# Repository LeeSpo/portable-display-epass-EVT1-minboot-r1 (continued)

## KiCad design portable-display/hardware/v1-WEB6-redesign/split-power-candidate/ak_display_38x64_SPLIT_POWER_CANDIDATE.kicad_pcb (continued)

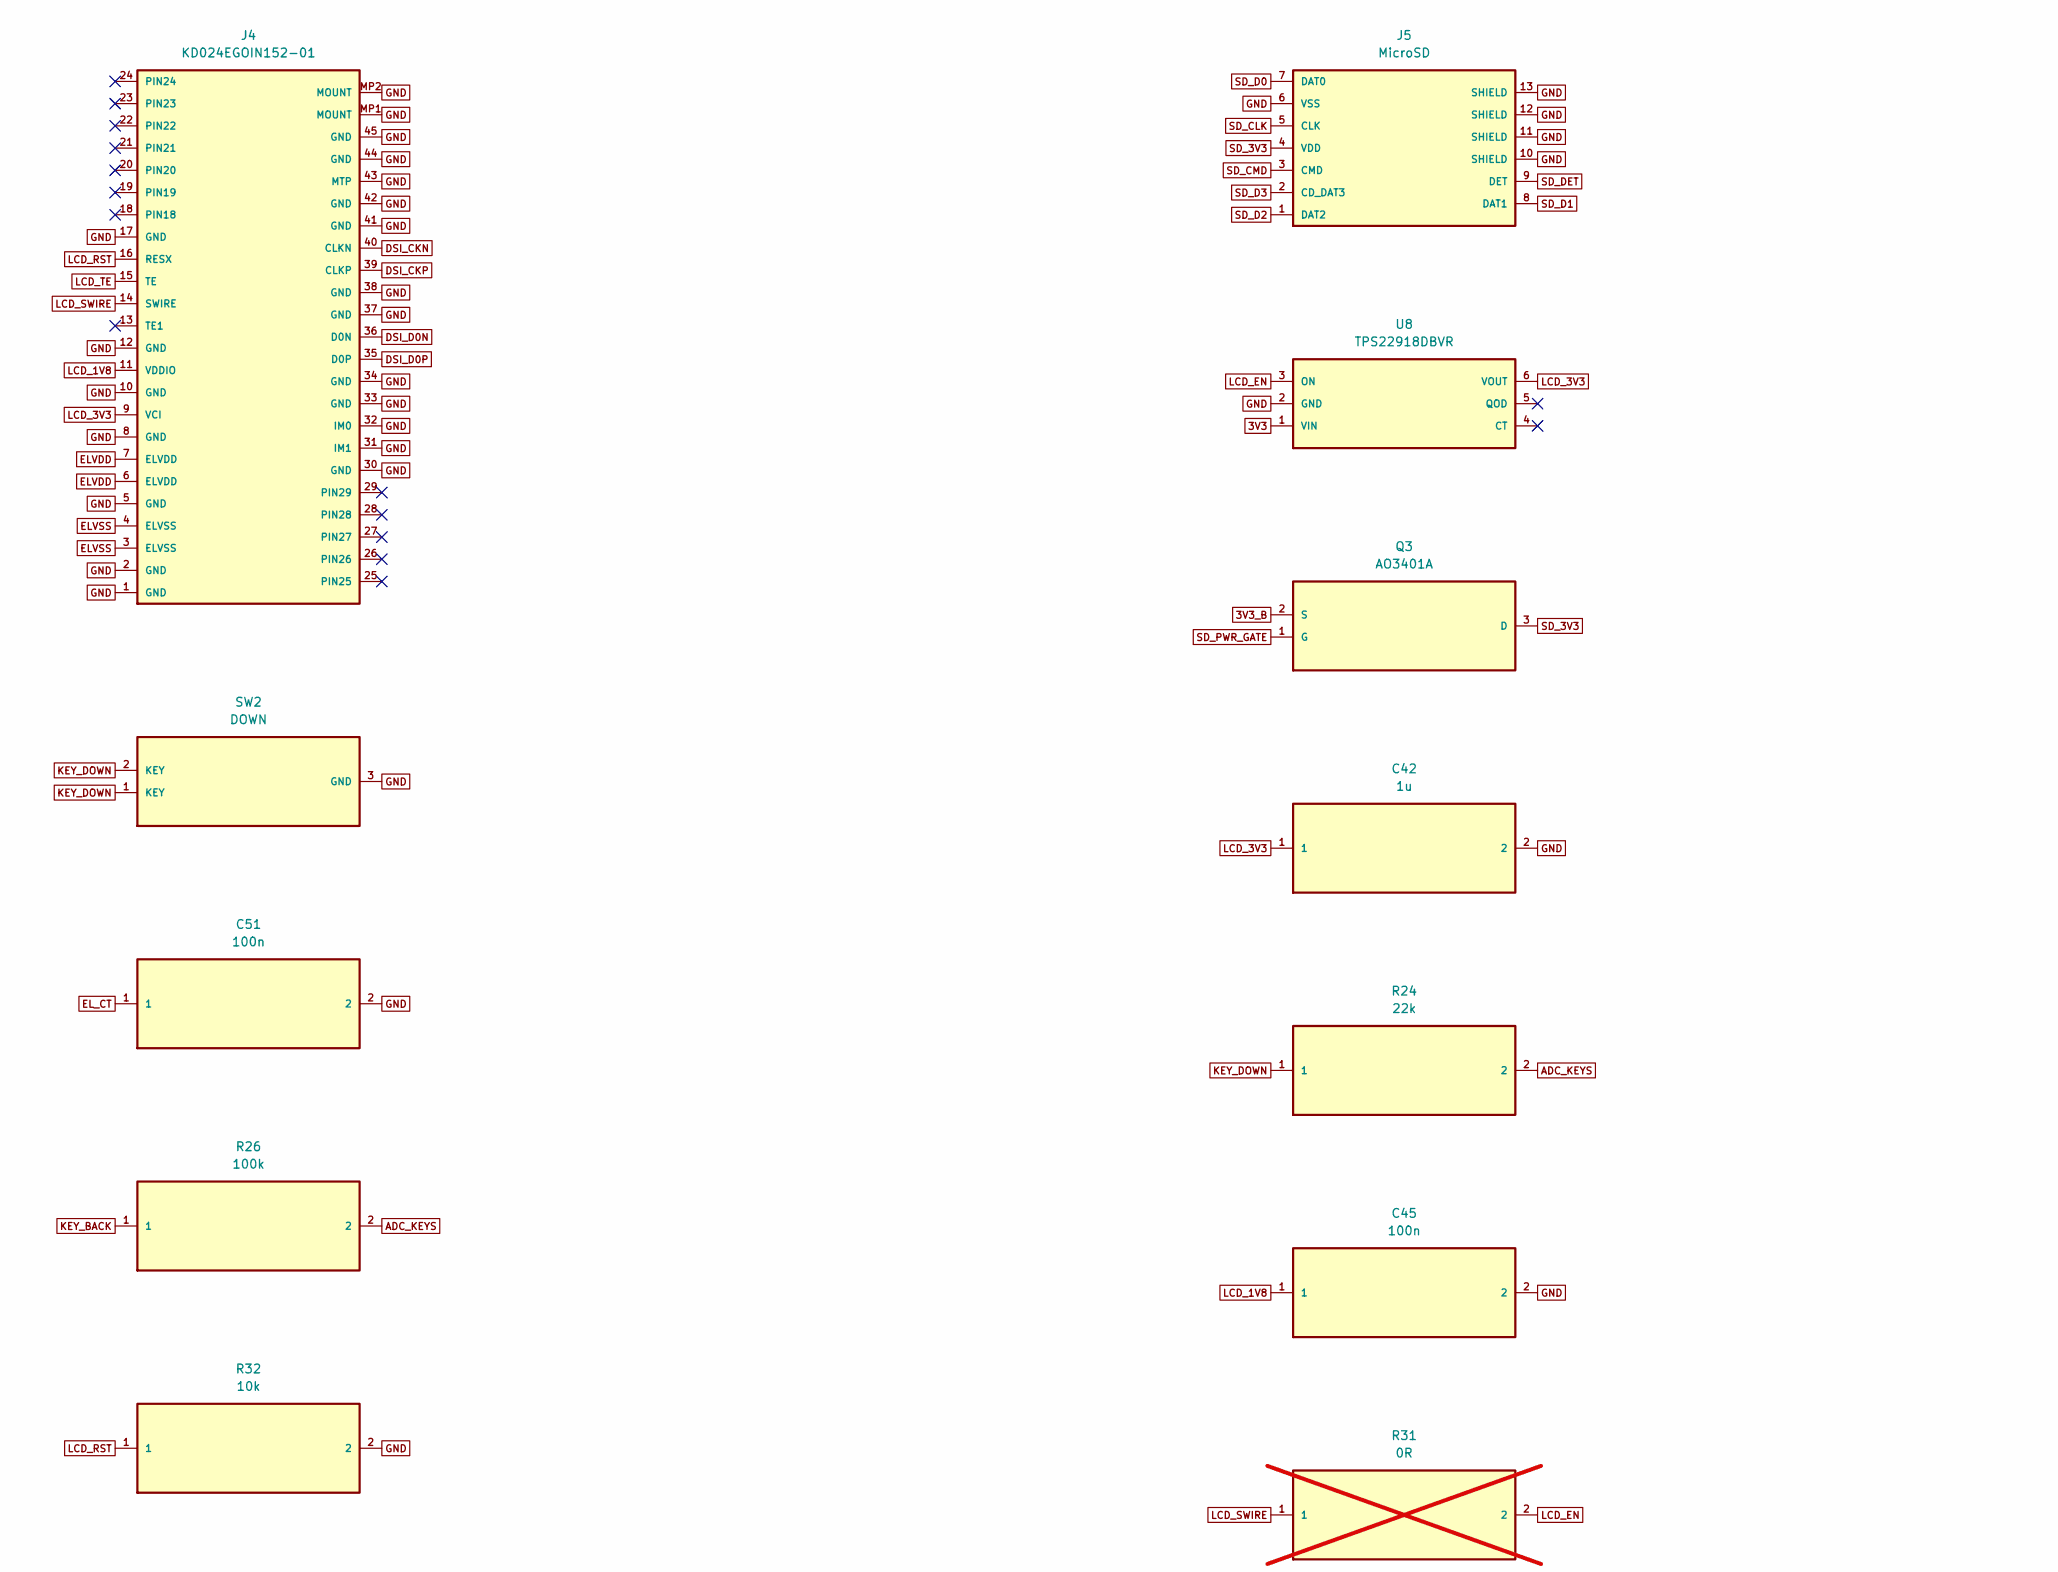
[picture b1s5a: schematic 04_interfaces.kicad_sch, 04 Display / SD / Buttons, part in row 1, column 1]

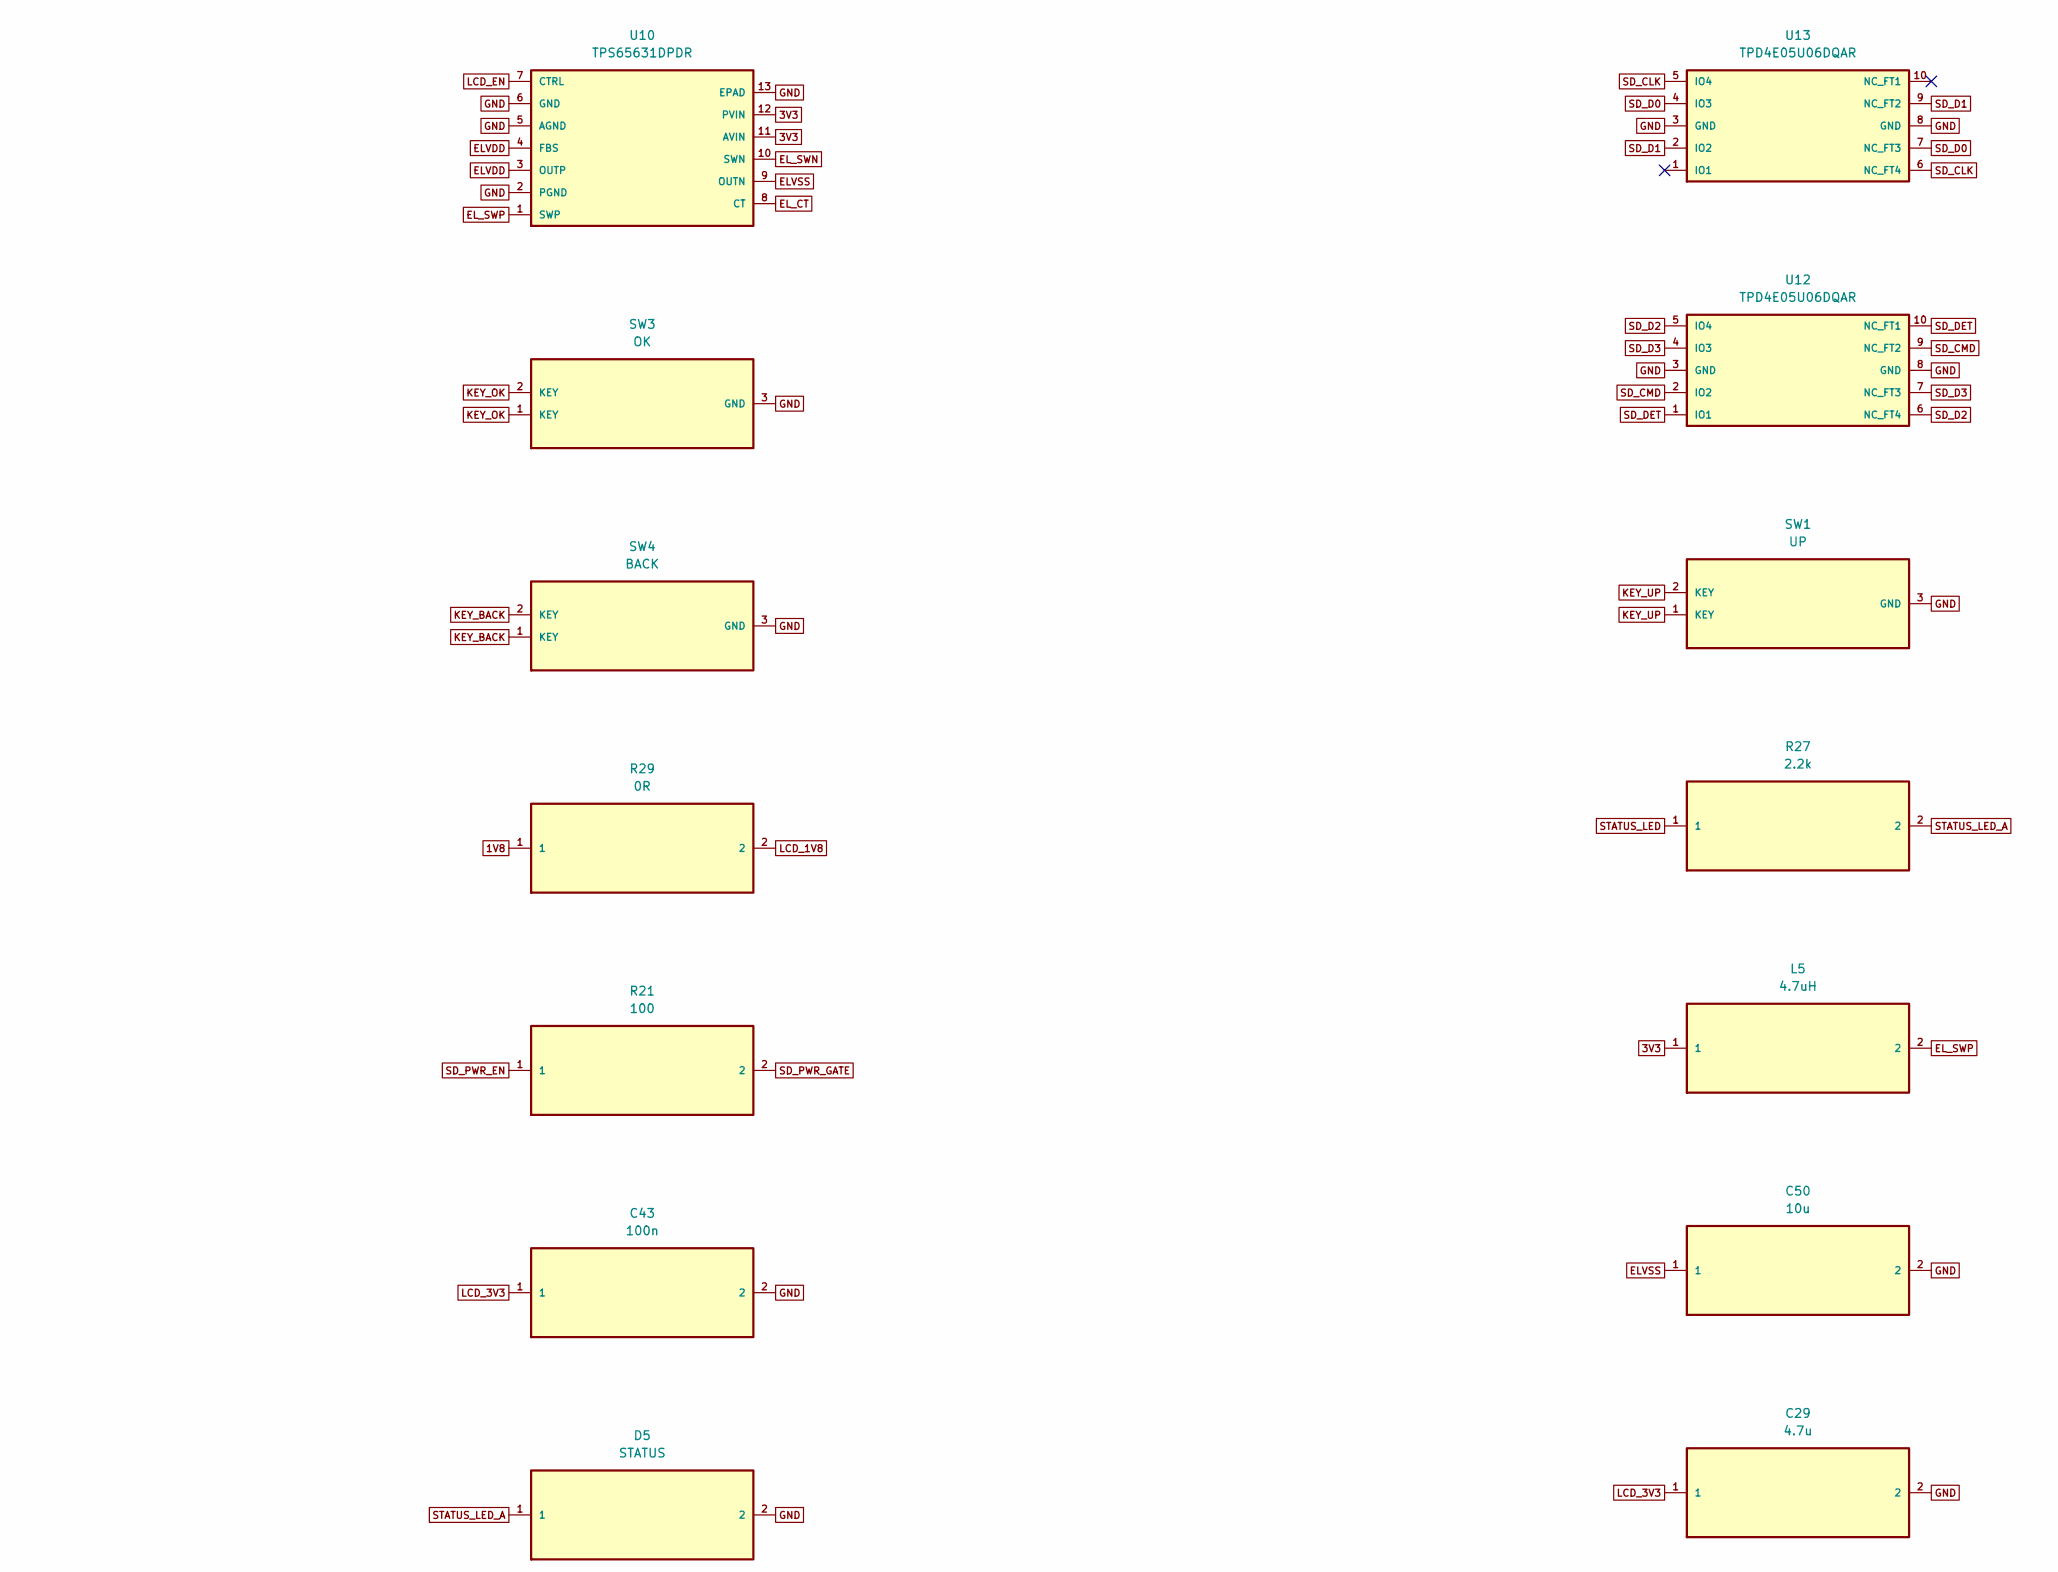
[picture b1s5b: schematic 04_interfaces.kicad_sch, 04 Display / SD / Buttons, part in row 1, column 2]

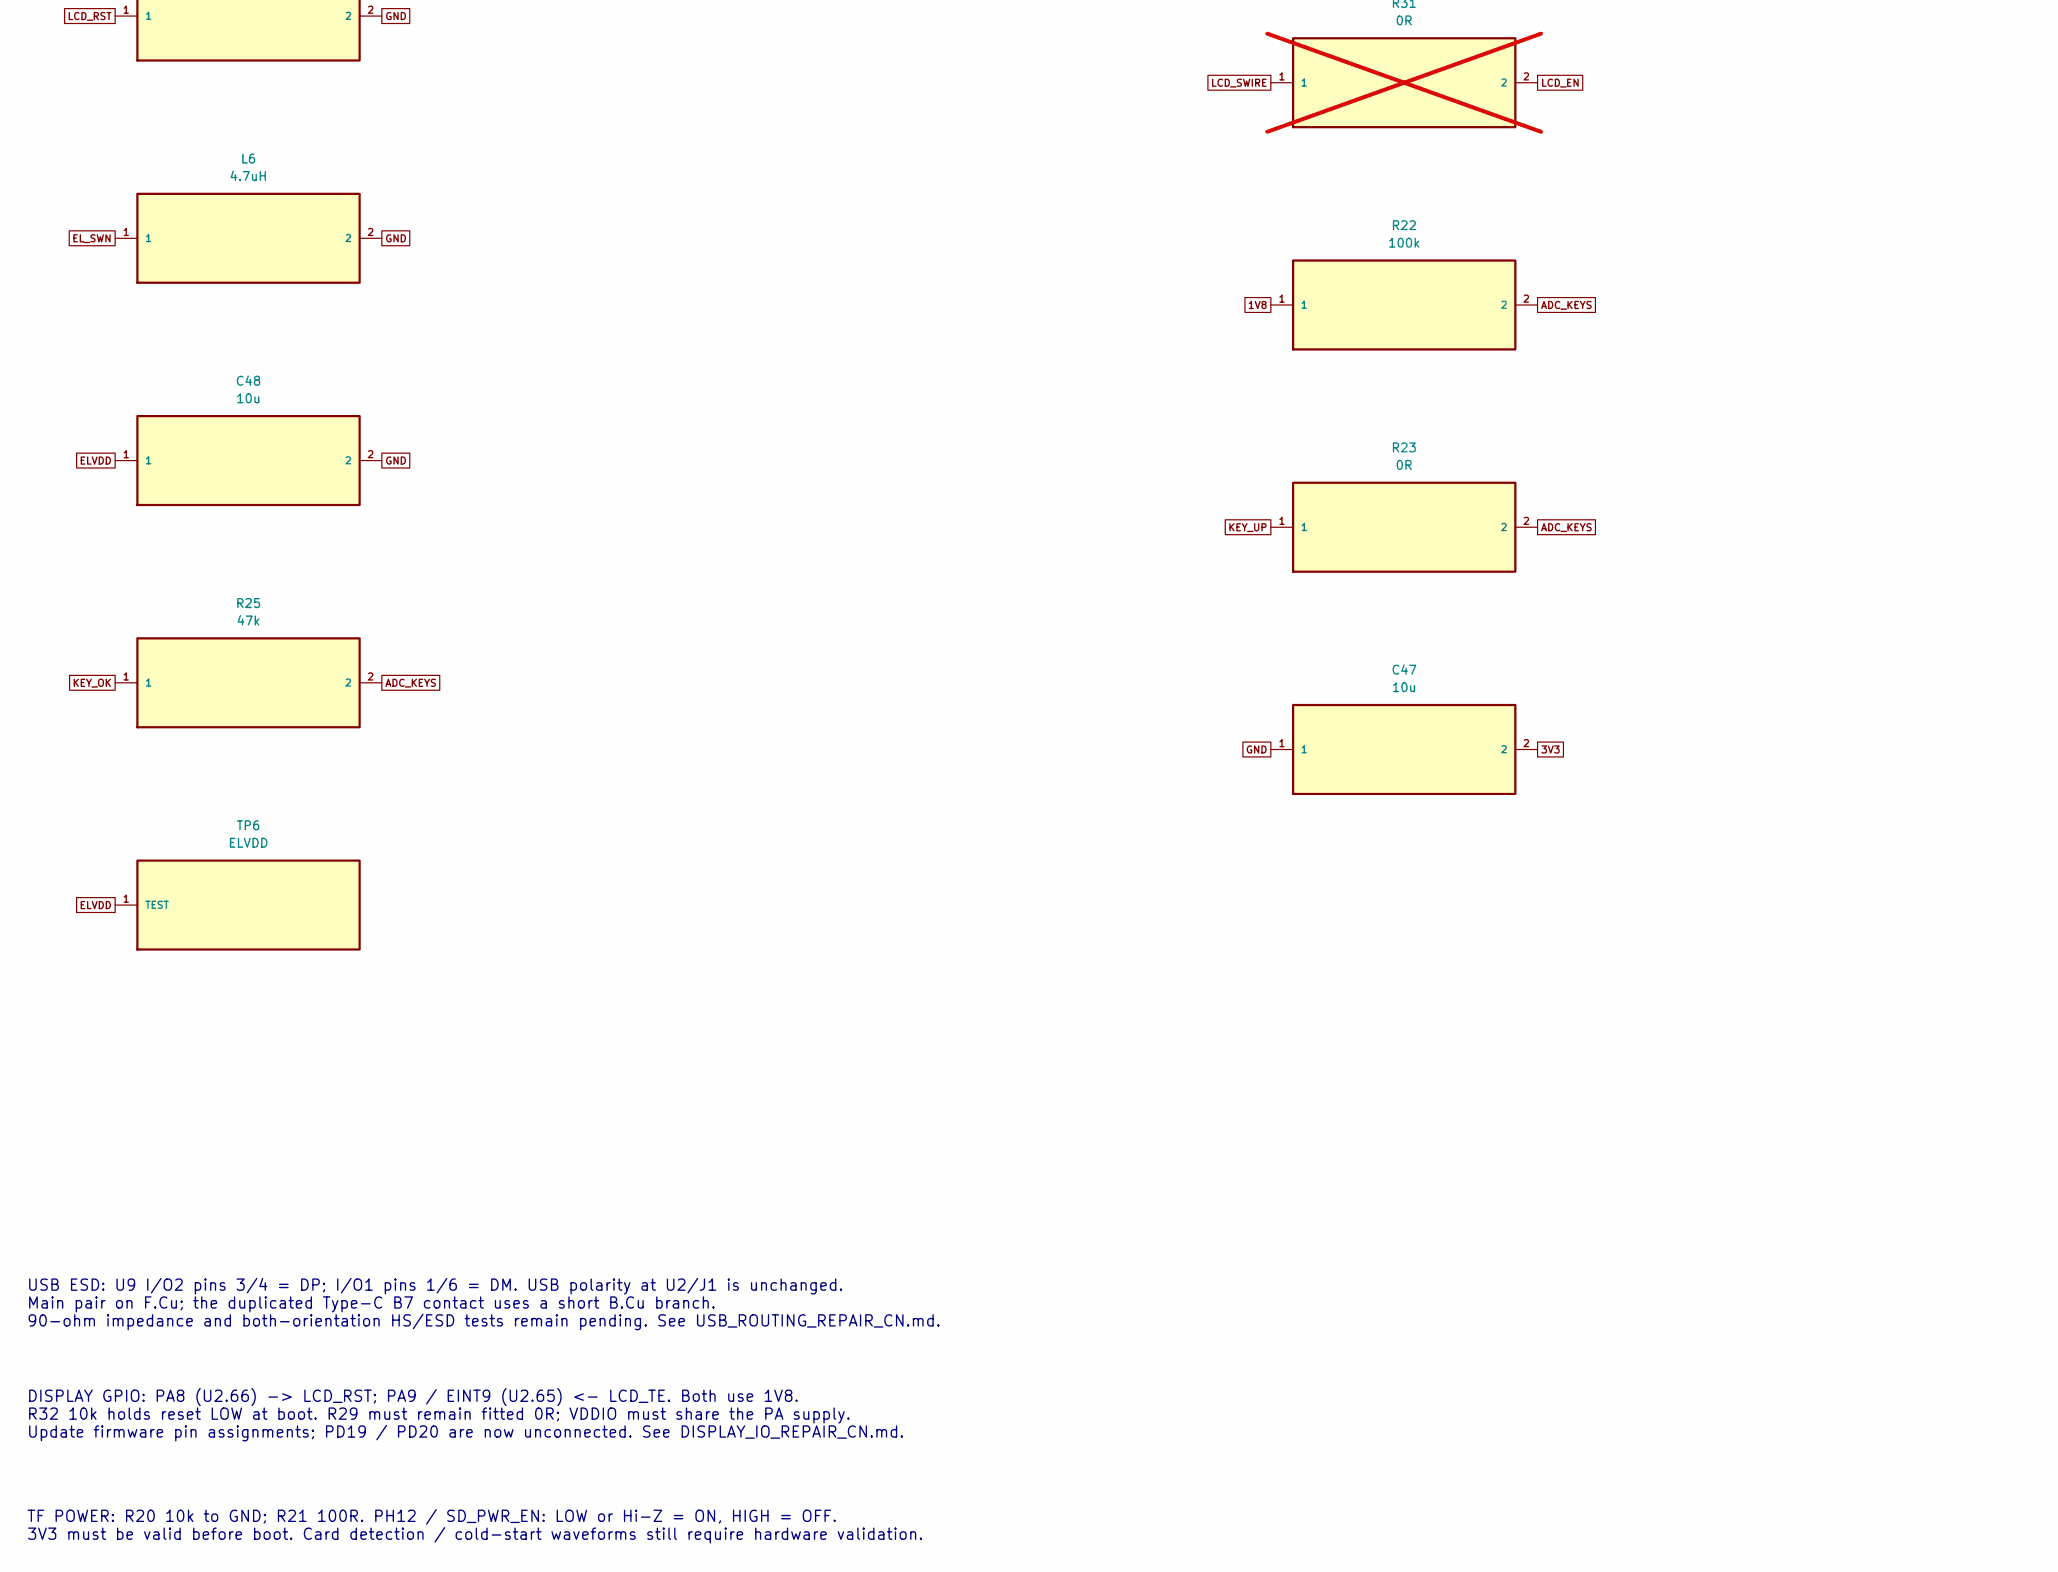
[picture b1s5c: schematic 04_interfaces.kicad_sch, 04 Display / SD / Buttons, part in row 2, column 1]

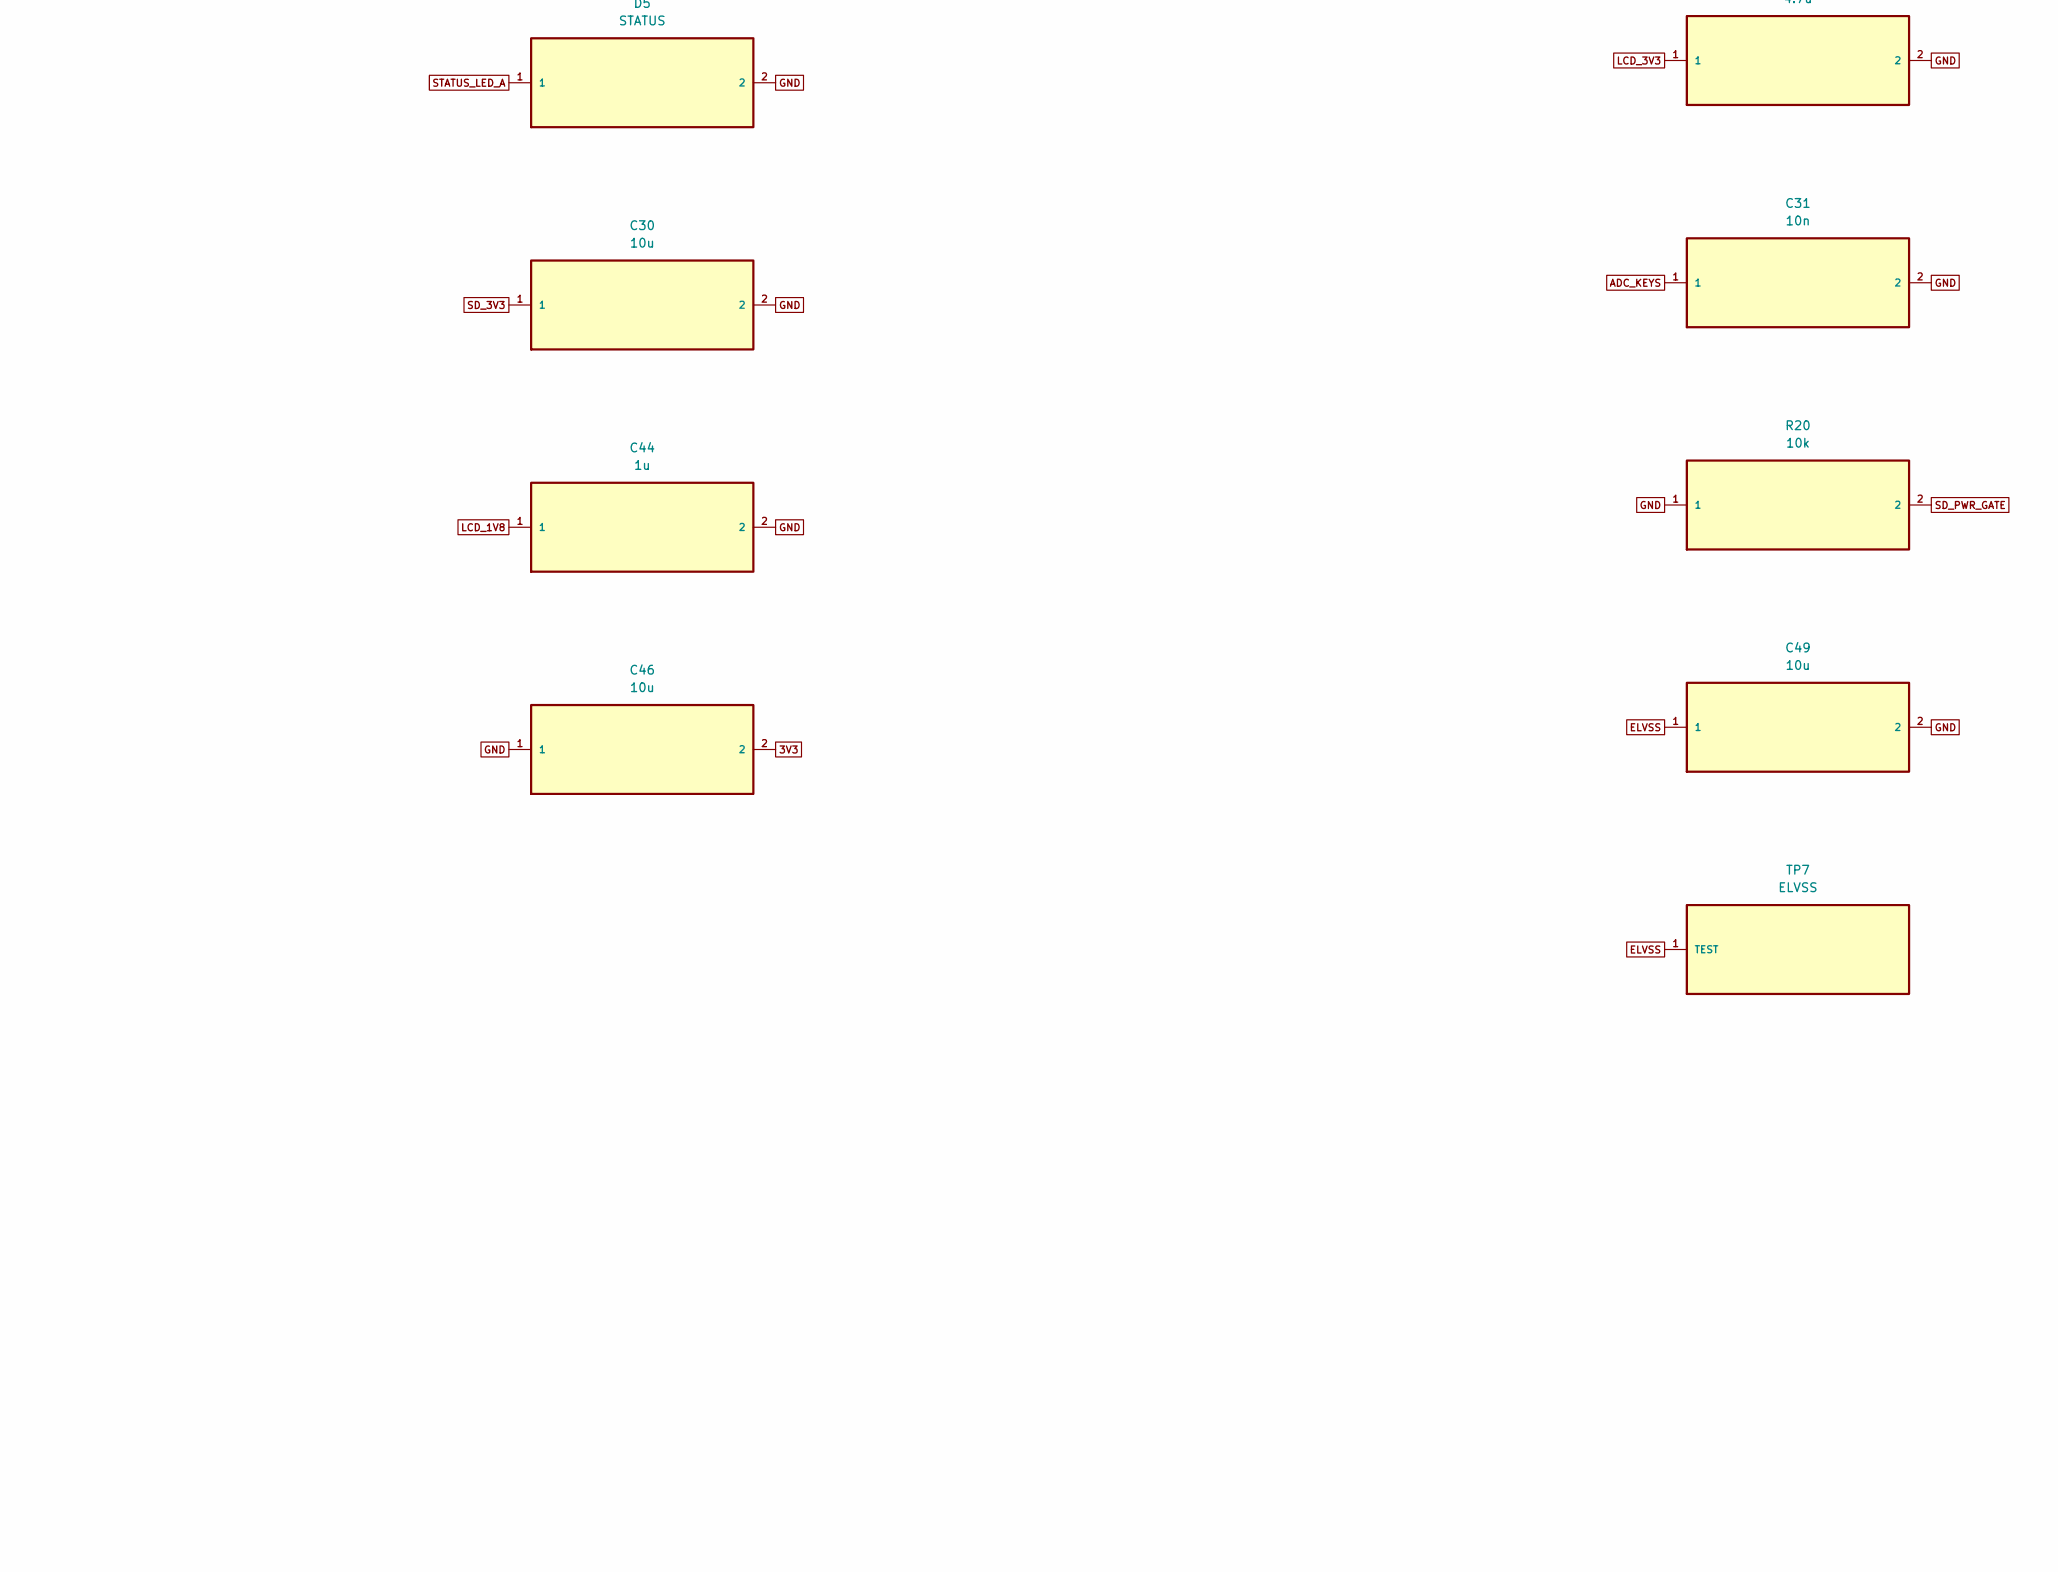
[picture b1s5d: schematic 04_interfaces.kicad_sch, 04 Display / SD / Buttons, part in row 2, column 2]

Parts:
C29: 4.7u; 0603; MPN CL10A475KO8NNNC; LCSC C19666
C30, C48, C49, C50: 10u; 0603; MPN CL10A106KP8NNNC; LCSC C19702
C31: 10n; 0402; MPN CL05B103KB5NNNC; LCSC C15195
C42, C44: 1u; 0603; MPN CL10A105KB8NNNC; LCSC C15849
C43, C45, C51: 100n; 0402; MPN CL05B104KO5NNNC; LCSC C1525
C46, C47: 10u; 0402; MPN CL05A106MQ5NUNC; LCSC C15525
D5: STATUS; LED0603; MPN KT-0603B; LCSC C2288
J4: KD024EGOIN152-01; FPC45; MPN 502598-4593; LCSC C5365339
J5: MicroSD; XKTF-0803-0; MPN XKTF-0803-0; LCSC C381083
L5, L6: 4.7uH; IND_2x2; MPN WPN201610U4R7MT; LCSC C97018
Q3: AO3401A; SOT23-3; MPN AO3401A; LCSC C15127
R20, R32: 10k; 0402; MPN 0402WGF1002TCE; LCSC C25744
R21: 100; 0402; MPN 0402WGF1000TCE; LCSC C25076
R22, R26: 100k; 0402; MPN 0402WGF1003TCE; LCSC C25741
R23, R29: 0R; 0402; MPN 0402WGF0000TCE; LCSC C17168
R24: 22k; 0402; MPN 0402WGF2202TCE; LCSC C25768
R25: 47k; 0402; MPN 0402WGF4702TCE; LCSC C25792
R27: 2.2k; 0402; MPN 0402WGF2201TCE; LCSC C25879
R31: 0R; 0402; not fitted
SW1: UP; SW_SIDE; MPN GT-TC072B-H045-L1; LCSC C5117859
SW2: DOWN; SW_SIDE; MPN GT-TC072B-H045-L1; LCSC C5117859
SW3: OK; SW_SIDE; MPN GT-TC072B-H045-L1; LCSC C5117859
SW4: BACK; SW_SIDE; MPN GT-TC072B-H045-L1; LCSC C5117859
TP6: ELVDD; TestPoint_Pad_D1.0mm
TP7: ELVSS; TestPoint_Pad_D1.0mm
U8: TPS22918DBVR; TPS22918_DBV6; MPN TPS22918DBVR; LCSC C131941
U10: TPS65631DPDR; WSON-12; MPN TPS65631DPDR; LCSC C165127
U12, U13: TPD4E05U06DQAR; TPD4E05U06_DQA; MPN TPD4E05U06DQAR; LCSC C138714

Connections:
1V8: R22.1, R29.1; also elsewhere on the board
3V3: C46.2, C47.2, L5.1, U8.1 (VIN), U10.11 (AVIN), U10.12 (PVIN); also elsewhere on the board
3V3_B: Q3.2 (S); also elsewhere on the board
ADC_KEYS: C31.1, R22.2, R23.2, R24.2, R25.2, R26.2; also elsewhere on the board
DSI_CKN: J4.40 (CLKN); also elsewhere on the board
DSI_CKP: J4.39 (CLKP); also elsewhere on the board
DSI_D0N: J4.36 (D0N); also elsewhere on the board
DSI_D0P: J4.35 (D0P); also elsewhere on the board
ELVDD: C48.1, J4.6 (ELVDD), J4.7 (ELVDD), TP6.1 (TEST), U10.3 (OUTP), U10.4 (FBS)
ELVSS: C49.1, C50.1, J4.3 (ELVSS), J4.4 (ELVSS), TP7.1 (TEST), U10.9 (OUTN)
EL_CT: C51.1, U10.8 (CT)
EL_SWN: L6.1, U10.10 (SWN)
EL_SWP: L5.2, U10.1 (SWP)
GND: C29.2, C30.2, C31.2, C42.2, C43.2, C44.2, C45.2, C46.1, C47.1, C48.2, C49.2, C50.2, C51.2, D5.2, J4.1 (GND), J4.2 (GND), J4.5 (GND), J4.8 (GND), J4.10 (GND), J4.12 (GND), J4.17 (GND), J4.30 (GND), J4.31 (IM1), J4.32 (IM0), J4.33 (GND), J4.34 (GND), J4.37 (GND), J4.38 (GND), J4.41 (GND), J4.42 (GND), J4.43 (MTP), J4.44 (GND), J4.45 (GND), J4.MP1 (MOUNT), J4.MP2 (MOUNT), J5.6 (VSS), J5.10 (SHIELD), J5.11 (SHIELD), J5.12 (SHIELD), J5.13 (SHIELD), L6.2, R20.1, R32.2, SW1.3 (GND), SW2.3 (GND), SW3.3 (GND), SW4.3 (GND), U8.2 (GND), U10.2 (PGND), U10.5 (AGND), U10.6 (GND), U10.13 (EPAD), U12.3 (GND), U12.8 (GND), U13.3 (GND), U13.8 (GND); also elsewhere on the board
KEY_BACK: R26.1, SW4.1 (KEY), SW4.2 (KEY)
KEY_DOWN: R24.1, SW2.1 (KEY), SW2.2 (KEY)
KEY_OK: R25.1, SW3.1 (KEY), SW3.2 (KEY)
KEY_UP: R23.1, SW1.1 (KEY), SW1.2 (KEY)
LCD_1V8: C44.1, C45.1, J4.11 (VDDIO), R29.2
LCD_3V3: C29.1, C42.1, C43.1, J4.9 (VCI), U8.6 (VOUT)
LCD_EN: R31.2, U8.3 (ON), U10.7 (CTRL); also elsewhere on the board
LCD_RST: J4.16 (RESX), R32.1; also elsewhere on the board
LCD_SWIRE: J4.14 (SWIRE), R31.1
LCD_TE: J4.15 (TE); also elsewhere on the board
SD_3V3: C30.1, J5.4 (VDD), Q3.3 (D)
SD_CLK: J5.5 (CLK), U13.5 (IO4), U13.6 (NC_FT4); also elsewhere on the board
SD_CMD: J5.3 (CMD), U12.2 (IO2), U12.9 (NC_FT2); also elsewhere on the board
SD_D0: J5.7 (DAT0), U13.4 (IO3), U13.7 (NC_FT3); also elsewhere on the board
SD_D1: J5.8 (DAT1), U13.2 (IO2), U13.9 (NC_FT2); also elsewhere on the board
SD_D2: J5.1 (DAT2), U12.5 (IO4), U12.6 (NC_FT4); also elsewhere on the board
SD_D3: J5.2 (CD_DAT3), U12.4 (IO3), U12.7 (NC_FT3); also elsewhere on the board
SD_DET: J5.9 (DET), U12.1 (IO1), U12.10 (NC_FT1); also elsewhere on the board
SD_PWR_EN: R21.1; also elsewhere on the board
SD_PWR_GATE: Q3.1 (G), R20.2, R21.2
STATUS_LED: R27.1; also elsewhere on the board
STATUS_LED_A: D5.1, R27.2

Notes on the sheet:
USB ESD: U9 I/O2 pins 3/4 = DP; I/O1 pins 1/6 = DM. USB polarity at U2/J1 is unchanged. Main pair on F.Cu; the duplicated Type-C B7 contact uses a short B.Cu branch. 90-ohm impedance and both-orientation HS/ESD tests remain pending. See USB_ROUTING_REPAIR_CN.md.
TF POWER: R20 10k to GND; R21 100R. PH12 / SD_PWR_EN: LOW or Hi-Z = ON, HIGH = OFF. 3V3 must be valid before boot. Card detection / cold-start waveforms still require hardware validation.
DISPLAY GPIO: PA8 (U2.66) -> LCD_RST; PA9 / EINT9 (U2.65) <- LCD_TE. Both use 1V8. R32 10k holds reset LOW at boot. R29 must remain fitted 0R; VDDIO must share the PA supply. Update firmware pin assignments; PD19 / PD20 are now unconnected. See DISPLAY_IO_REPAIR_CN.md.

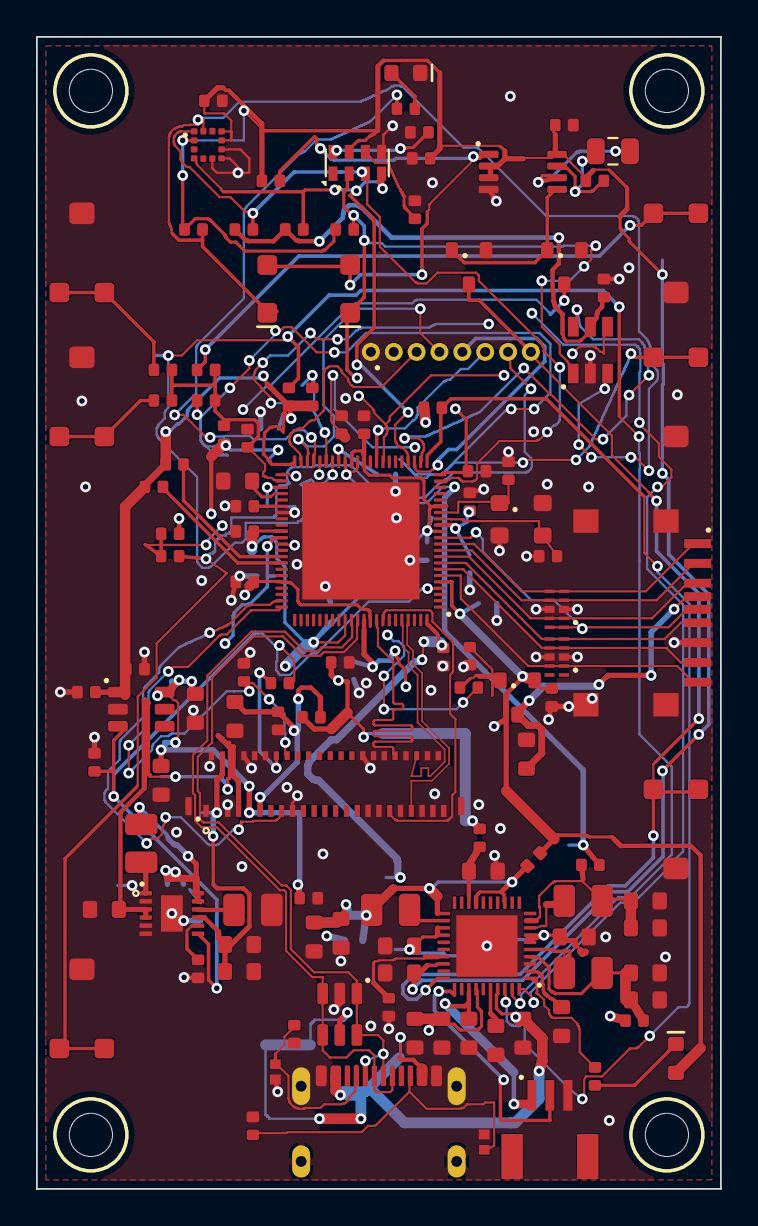
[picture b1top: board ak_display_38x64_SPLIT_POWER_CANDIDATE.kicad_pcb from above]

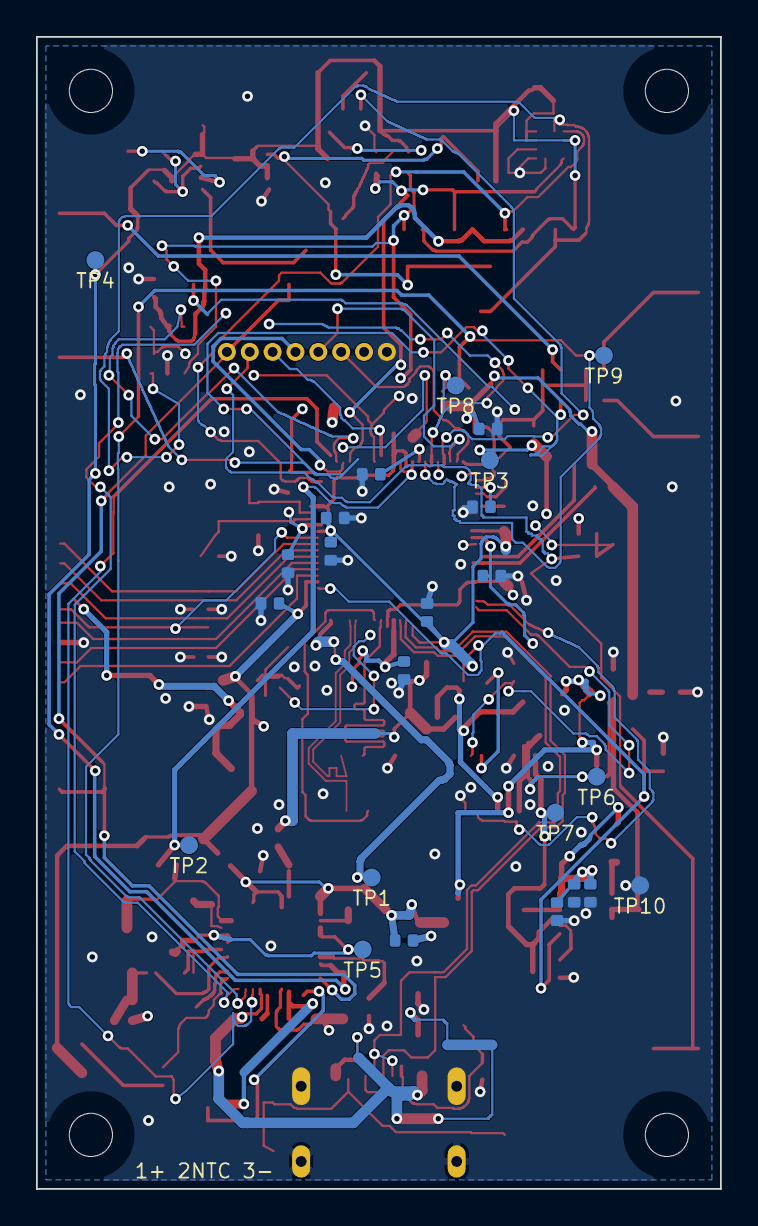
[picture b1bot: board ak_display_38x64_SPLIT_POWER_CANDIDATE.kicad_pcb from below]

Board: 4 copper layers, 38.0 x 64.0 mm, 147 parts (24 on the bottom side), 89 nets.

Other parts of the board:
H1: M2; MountingHole_1
H2: M2; MountingHole_2
H3: M2; MountingHole_3
H4: M2; MountingHole_4

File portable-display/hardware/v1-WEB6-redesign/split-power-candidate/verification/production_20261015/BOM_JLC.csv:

Comment,Designator,Footprint,LCSC Part #,Quantity
22u,"C1,C2",0603,C86295,2
1u,"C3,C11,C33,C40,C41,C42,C44",0603,C15849,7
22u,"C4,C5,C6,C7,C8,C9",0603,C59461,6
2.2u,"C10,C35,C38",0603,C23630,3
18p,"C12,C13",0402,C1549,2
100n,"C14,C15,C16,C17,C18,C19,C20,C21,C24,C25,C26,C37,C39,C43,C45,C51,C52,C54,C55,C56,C57,C58,C59,C60,C61,C62,C63",0402,C1525,27
3.3u,C23,C_0805_2012Metric,C7393948,1
4.7u,C29,0603,C19666,1
10u,"C30,C32,C48,C49,C50",0603,C19702,5
10n,C31,0402,C15195,1
2.2u,C34,0402,C12530,1
470n,C36,0402,C47339,1
10u,"C46,C47",0402,C15525,2
1u,C53,0402,C52923,1
CHARGE,D1,LED0603,C12624,1
BAT54,"D2,D3",D_SOD123,C699107,2
STATUS,D5,LED0603,C2288,1
ESDLC5V0LB,"D13,D14",DFN1006-2,C20168172,2
USB4105-GF-A-060,J1,USB4105,C3025063,1
1S LiPo + NTC,J2,SH1.0_3P_RA,C7430445,1
KD024EGOIN152-01,J4,FPC45,C5365339,1
MicroSD,J5,XKTF-0803-0,C381083,1
1uH/2A,"L1,L2,L3",IND_2x2,C97002,3
4.7uH,"L5,L6",IND_2x2,C97018,2
2N7002,"Q1,Q2",SOT23-3,C8545,2
AO3401A,Q3,SOT23-3,C15127,1
5.1k,"R1,R2",0402,C25905,2
4.7k,"R3,R15,R16",0402,C25900,3
2.2k,"R4,R5,R6,R27",0402,C25879,4
10k,"R10,R11,R13,R14,R17,R18,R20,R28,R32,R34,R35",0402,C25744,11
910k,R12,0402,C352384,1
100,R21,0402,C25076,1
100k,"R22,R26",0402,C25741,2
0R,"R23,R29,R36,R37,R38,R39,R40",0402,C17168,7
22k,R24,0402,C25768,1
47k,R25,0402,C25792,1
1k,R33,0402,C11702,1
UP,SW1,SW_SIDE,C5117859,1
DOWN,SW2,SW_SIDE,C5117859,1
OK,SW3,SW_SIDE,C5117859,1
BACK,SW4,SW_SIDE,C5117859,1
POWER,SW5,SW_SIDE,C5117859,1
FEL,SW6,SW_SIDE,C5117859,1
AXP2101,U1,QFN40,C3036461,1
V851s,U2,QFN88,C5365286,1
LIS2DW12TR,U4,LGA-12,C189624,1
RV-3028-C7,U5,RTC-8,C3019759,1
SN74LVC1G123DCTR,U6,SN74LVC1G123_DCT8,C123302,1
TPS22918DBVR,U8,TPS22918_DBV6,C131941,1
USBLC6-2SC6,U9,USBLC6-2SC6_SOT23-6,C2827654,1
TPS65631DPDR,U10,WSON-12,C165127,1
SN74LVC2G17DBVR,U11,SN74LVC2G17_DBV6,C10429,1
TPD4E05U06DQAR,"U12,U13",TPD4E05U06_DQA,C138714,2
24MHz 10ppm,Y1,XTAL4,C16197264,1
